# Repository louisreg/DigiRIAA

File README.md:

# DigiRIAA
A small and compact RIAA preamp with digital outputs
blablabla

## Description
schematic etc

## PCB

## Measures

## TODO
  - Get rid of STM32 HAL lib, add CMAKE, clean etc. 
  - Remove TL072 buffer from PCB
  - Remove USB-C connector

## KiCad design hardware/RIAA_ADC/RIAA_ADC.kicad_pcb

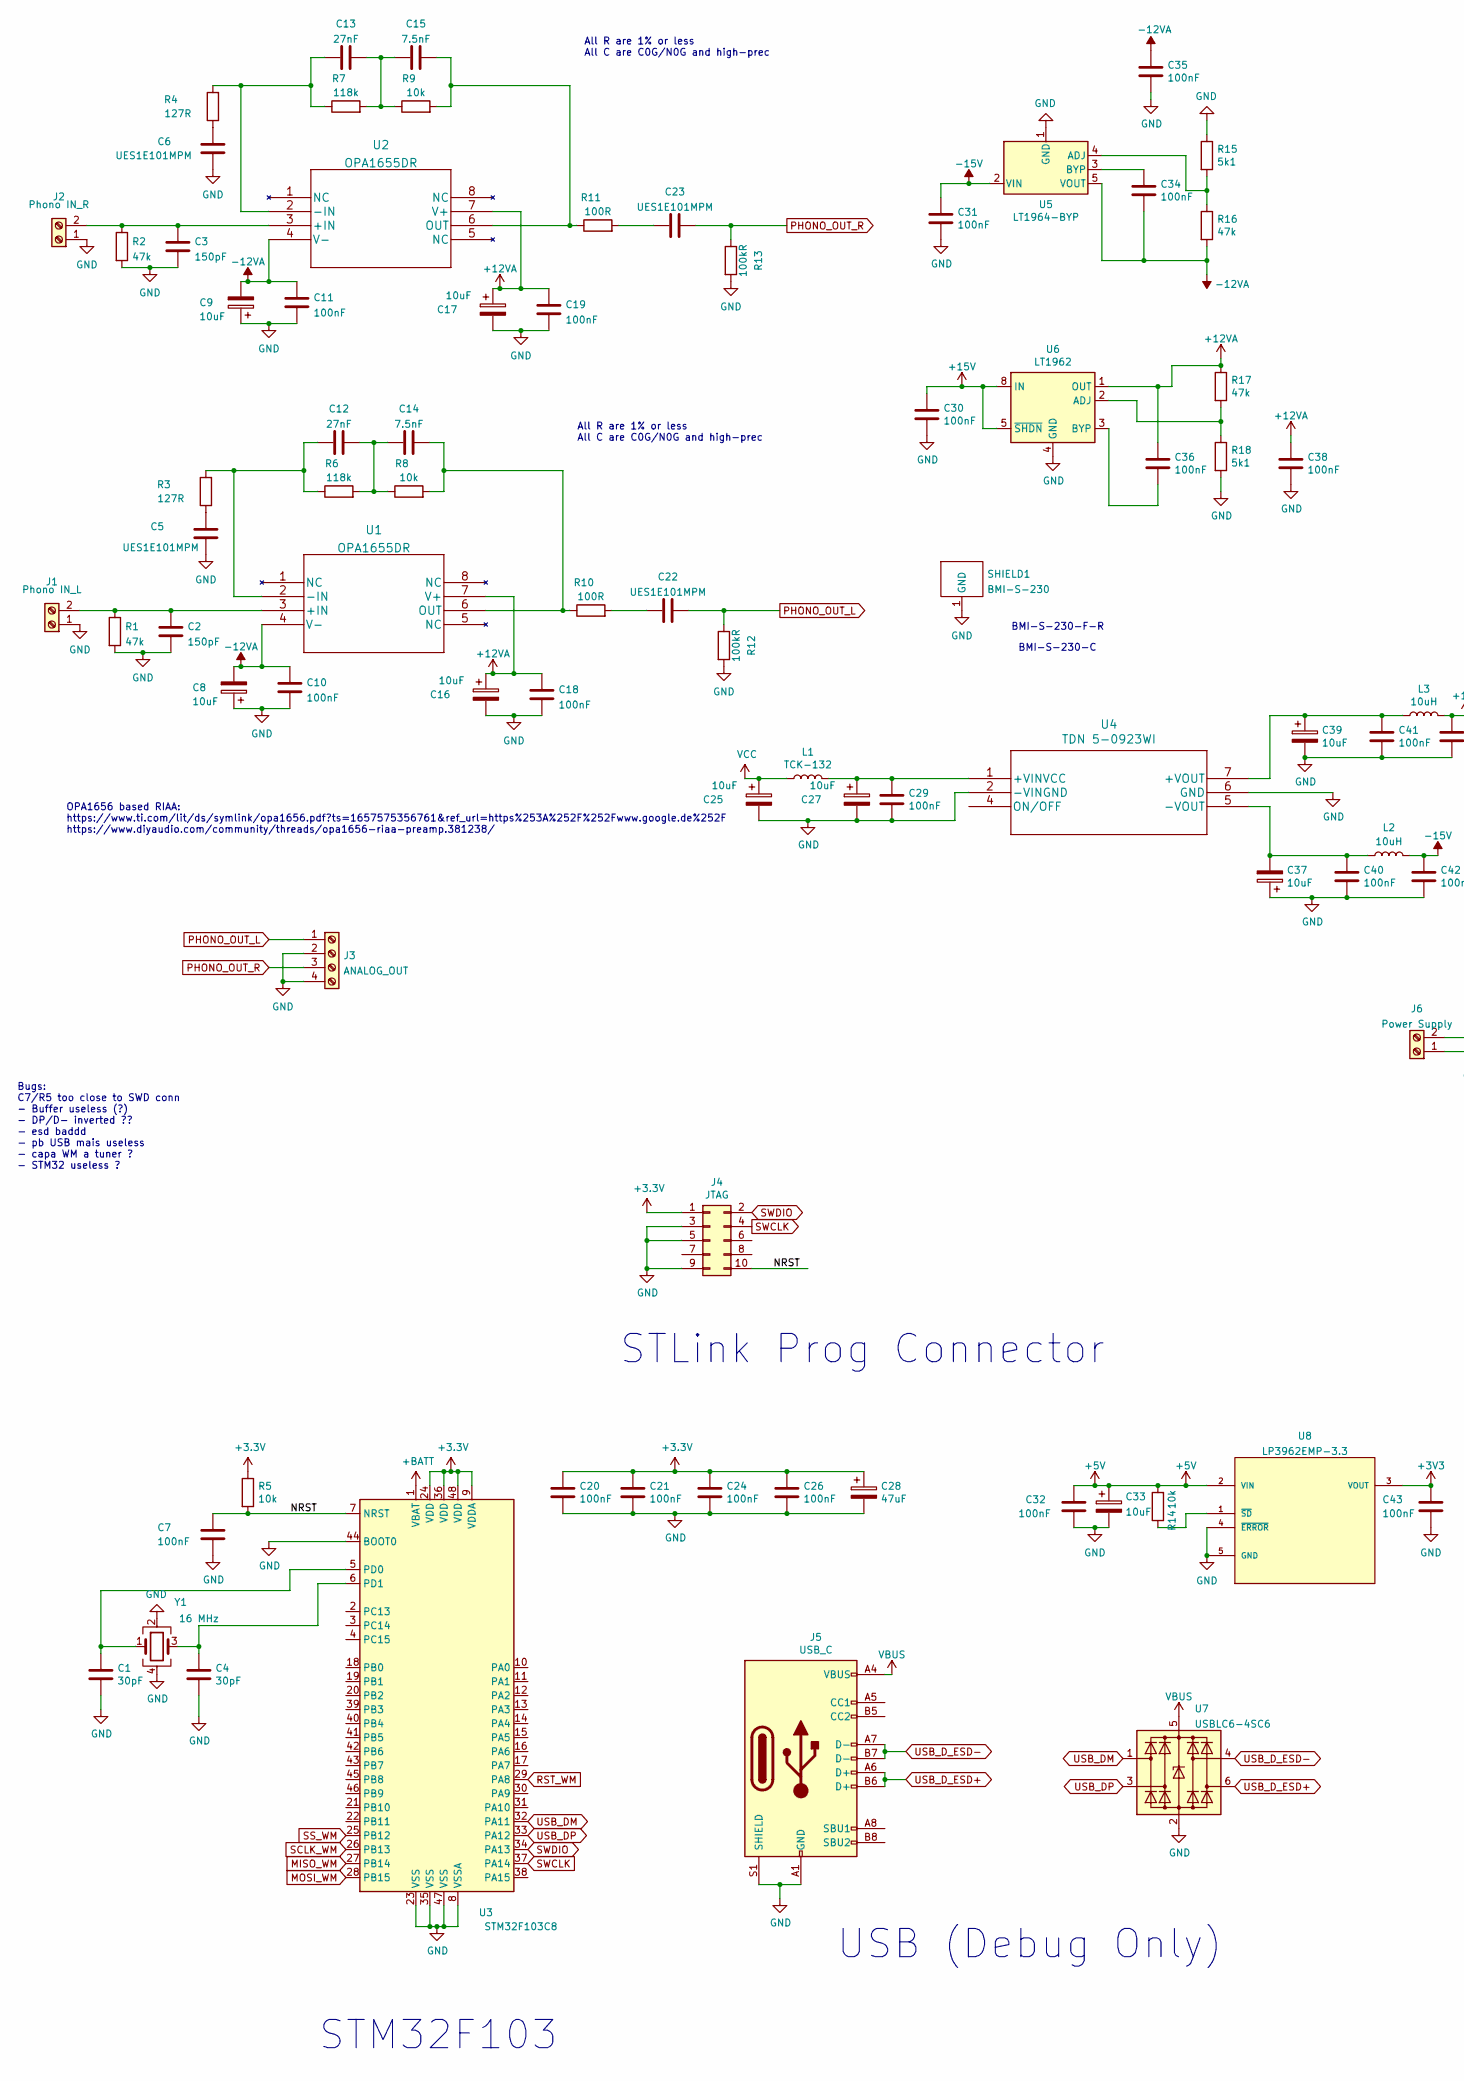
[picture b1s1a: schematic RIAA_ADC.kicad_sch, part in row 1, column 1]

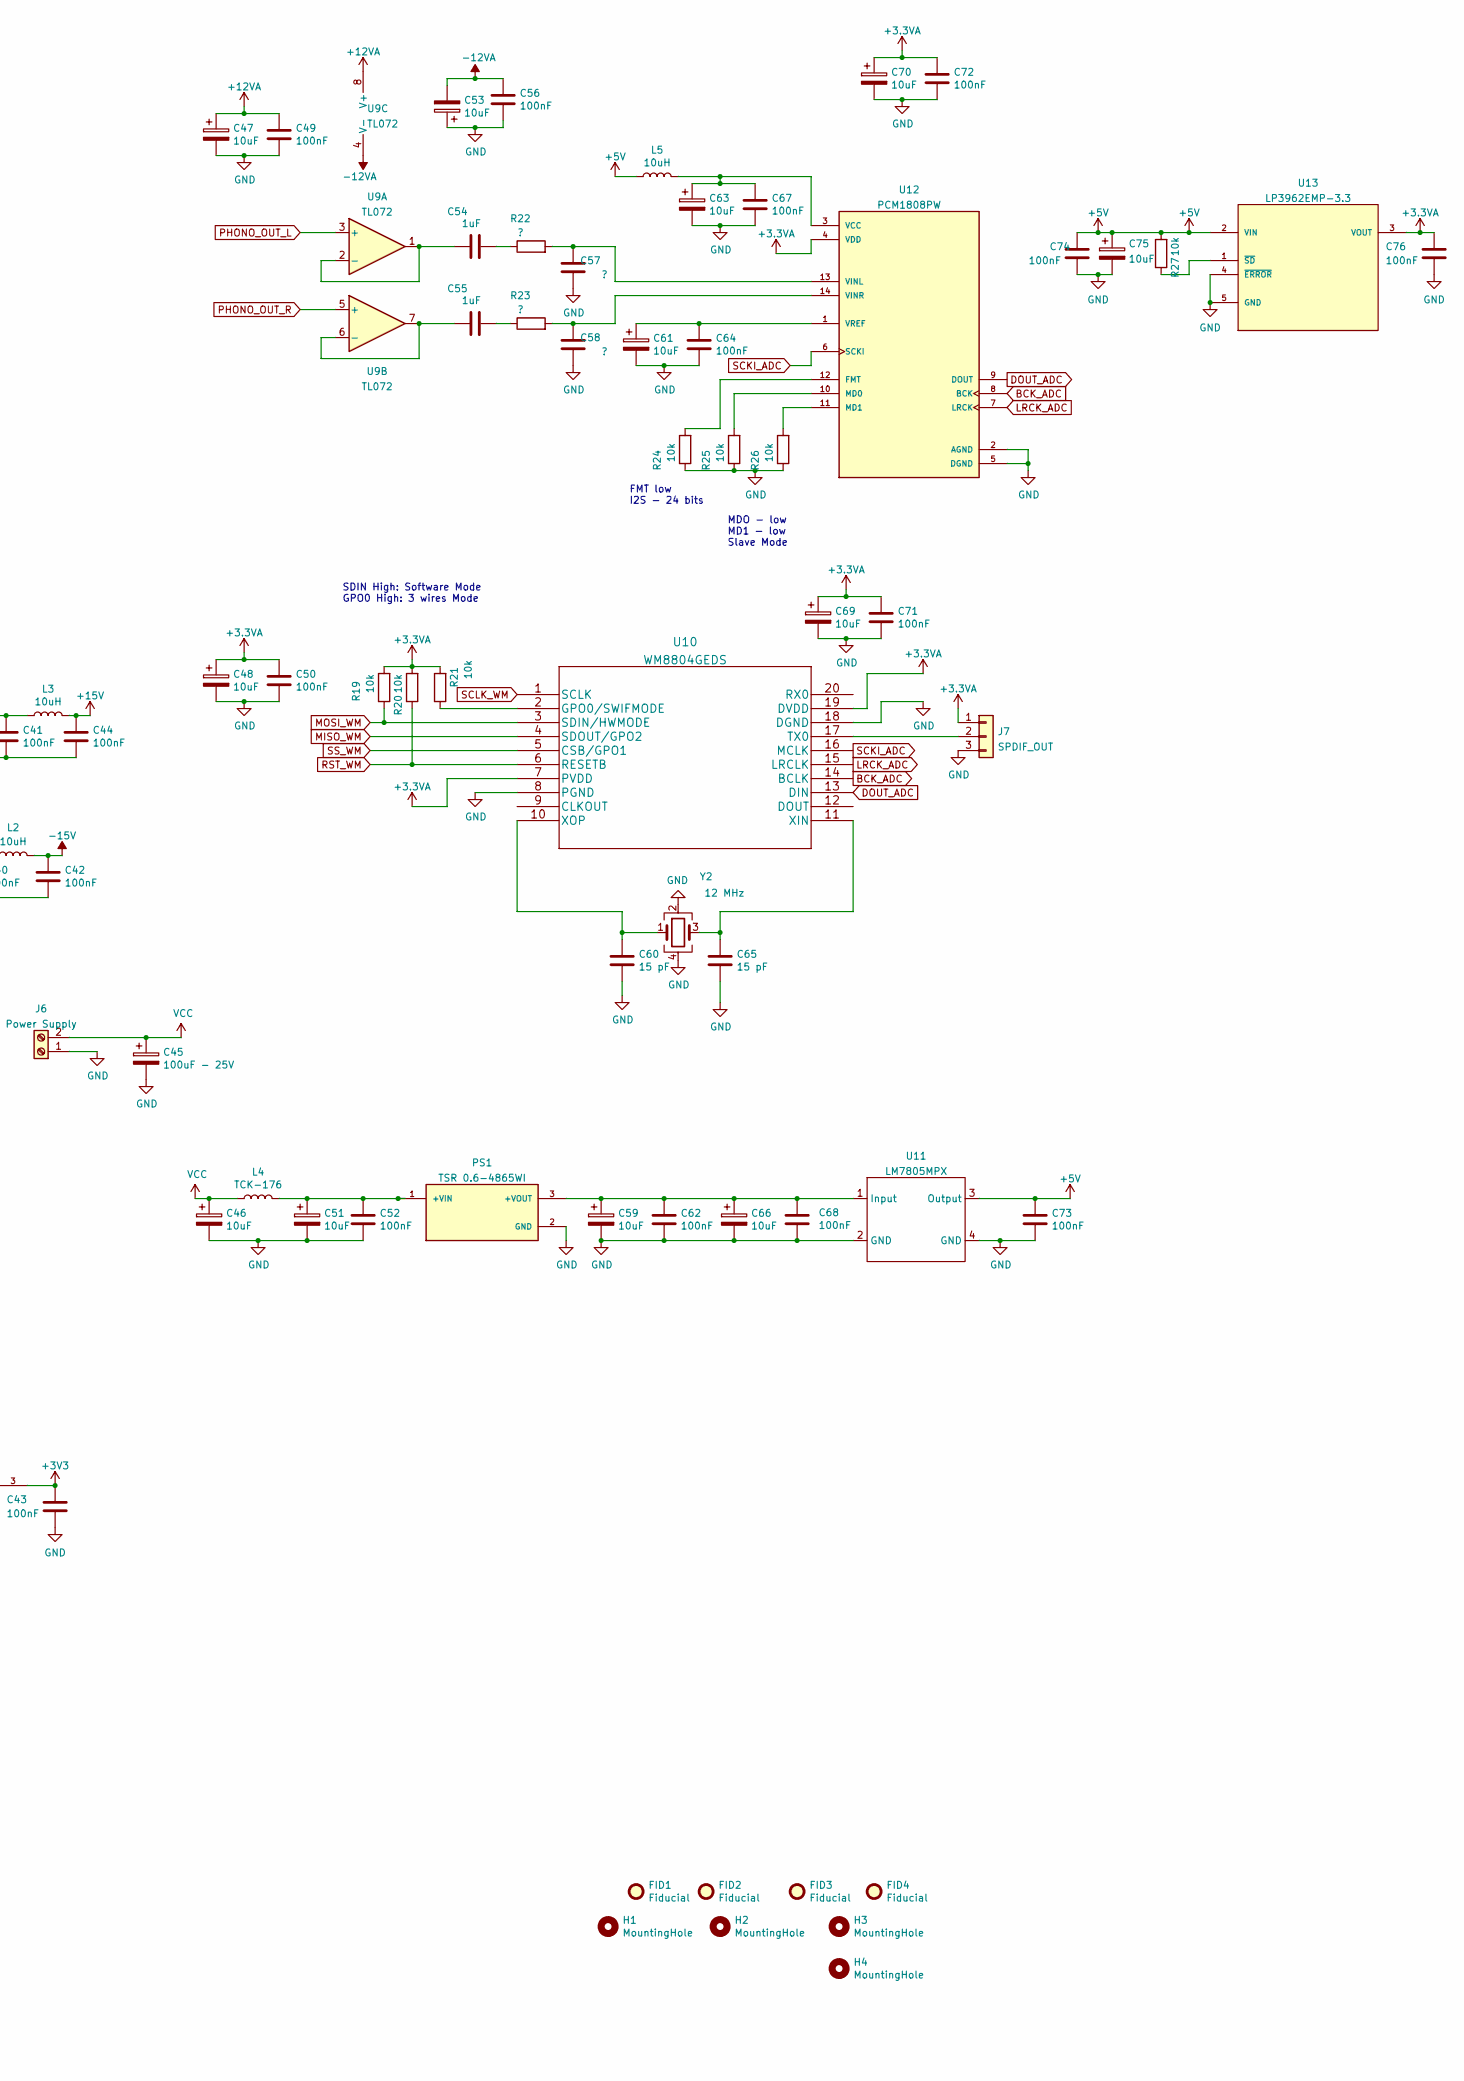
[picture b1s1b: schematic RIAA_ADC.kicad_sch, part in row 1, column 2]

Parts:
C1, C4: 30pF; C_0603_1608Metric
C2, C3: 150pF; C_0603_1608Metric
C5, C6, C22, C23: UES1E101MPM; CP_Radial_D8.0mm_P5.00mm
C7, C10, C11, C18, C19, C20, C21, C24, C26, C29, C30, C31, C32, C34, C35, C36, C38, C40, C41, C42, C43, C44, C49, C50, C52, C56, C62, C64, C67, C68, C71, C72, C73, C74, C76: 100nF; C_0603_1608Metric
C8, C9, C16, C17, C25, C27, C33, C37, C39, C46, C47, C48, C51, C53, C59, C61, C63, C66, C69, C70, C75: 10uF; CP_EIA-3528-21_Kemet-B
C12, C13: 27nF; C_1210_3225Metric_Pad1.33x2.70mm_HandSolder
C14, C15: 7.5nF; C_1210_3225Metric_Pad1.33x2.70mm_HandSolder
C28: 47uF; CP_EIA-3528-21_Kemet-B
C45: 100uF - 25V; CP_Radial_D8.0mm_P5.00mm
C54, C55: 1uF; C_1210_3225Metric_Pad1.33x2.70mm_HandSolder
C57, C58: ?; C_0603_1608Metric
C60, C65: 15 pF; C_0603_1608Metric
FID1, FID2, FID3, FID4: Fiducial; Fiducial_0.5mm_Mask1mm
H1, H2, H3, H4: MountingHole; MountingHole_3mm
J1: Phono IN_L; TerminalBlock_TE_282834-2_1x02_P2.54mm_Horizontal
J2: Phono IN_R; TerminalBlock_TE_282834-2_1x02_P2.54mm_Horizontal
J3: ANALOG_OUT; TerminalBlock_TE_282834-4_1x04_P2.54mm_Horizontal
J4: JTAG; PinHeader_2x05_P1.27mm_Vertical_SMD
J5: USB_C; USB_C_Receptacle_XKB_U262-16XN-4BVC11
J6: Power Supply; TerminalBlock_bornier-2_P5.08mm
J7: SPDIF_OUT; TerminalBlock_TE_282834-3_1x03_P2.54mm_Horizontal
L1: TCK-132
L2, L3, L5: 10uH; L_1210_3225Metric
L4: TCK-176
PS1: TSR 0.6-4865WI; CONV_TSR_0.6-4833WI; PARTREV Apr 27, 2020
R1, R2, R16, R17: 47k; R_0603_1608Metric
R3, R4: 127R; R_0603_1608Metric
R5, R8, R9, R14, R19, R20, R21, R24, R25, R26, R27: 10k; R_0603_1608Metric
R6, R7: 118k; R_0603_1608Metric
R10, R11: 100R; R_0603_1608Metric
R12, R13: 100kR; R_0603_1608Metric
R15, R18: 5k1; R_0603_1608Metric
R22, R23: ?; R_0603_1608Metric
SHIELD1: BMI-S-230; Laird_Technologies_BMI-S-230-F_50.8x38.1mm
U1, U2: OPA1655DR
U3: STM32F103C8; LQFP-48_7x7mm_P0.5mm
U4: TDN 5-0923WI; Converter_DCDC_TRACO_TDN_5-xxxxWI_THT
U5: LT1964-BYP; TSOT-23-5
U6: LT1962; MSOP-8_3x3mm_P0.65mm
U7: USBLC6-4SC6; SOT-23-6
U8, U13: LP3962EMP-3.3; SOT150P696X180-5N; MPN LP3962EMP-3.3
U9: TL072; TSSOP-8_4.4x3mm_P0.65mm
U10: WM8804GEDS
U11: LM7805MPX; SOT-223
U12: PCM1808PW; SOP65P640X120-14N; PARTREV B
Y1: 16 MHz; Crystal_SMD_3225-4Pin_3.2x2.5mm_HandSoldering
Y2: 12 MHz; Crystal_SMD_3225-4Pin_3.2x2.5mm_HandSoldering

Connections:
+3.3VA: C48.1, C50.1, C69.1, C70.1, C71.1, C72.1, C76.1, J7.1, R19.2, R20.2, R21.2, U10.7 (PVDD), U10.19 (DVDD), U12.4 (VDD), U13.3 (VOUT)
+5V: C32.1, C33.1, C73.1, C74.1, C75.1, L5.1, R14.2, R27.2, U8.2 (VIN), U11.3 (Output), U13.2 (VIN)
+12VA: C16.1, C17.1, C18.1, C19.1, C36.1, C38.1, C47.1, C49.1, R17.1, U1.7 (V+), U2.7 (V+), U6.1 (OUT), U9.8 (V+)
+15V: C30.1, C44.1, L3.2, U6.5 (~SHDN), U6.8 (IN)
+BATT: U3.1 (VBAT)
-12VA: C8.2, C9.2, C10.1, C11.1, C34.2, C35.1, C53.2, C56.1, R16.2, U1.4 (V-), U2.4 (V-), U5.5 (VOUT), U9.4 (V-)
-15V: C31.1, C42.1, L2.2, U5.2 (VIN)
/NRST: C7.2, J4.10, R5.2, U3.7 (NRST)
BCK_ADC: U10.14 (BCLK), U12.8 (BCK)
DOUT_ADC: U10.13 (DIN), U12.9 (DOUT)
GND: C1.1, C2.2, C3.2, C4.1, C5.2, C6.2, C7.1, C8.1, C9.1, C10.2, C11.2, C16.2, C17.2, C18.2, C19.2, C20.1, C21.1, C24.1, C25.2, C26.1, C27.2, C28.2, C29.2, C30.2, C31.2, C32.2, C33.2, C35.2, C37.1, C38.2, C39.2, C40.2, C41.2, C42.2, C43.2, C44.2, C45.2, C46.2, C47.2, C48.2, C49.2, C50.2, C51.2, C52.2, C53.1, C56.2, C57.1, C58.1, C59.2, C60.1, C61.2, C62.2, C63.2, C64.2, C65.1, C66.2, C67.2, C68.2, C69.2, C70.2, C71.2, C72.2, C73.2, C74.2, C75.2, C76.2, J1.1, J2.1, J3.2, J3.4, J4.3, J4.5, J4.9, J5.A1 (GND), J5.A12 (GND), J5.B1 (GND), J5.B12 (GND), J5.S1 (SHIELD), J6.1, J7.3, PS1.2 (GND), R1.2, R2.2, R12.2, R13.2, R15.1, R18.2, R24.1, R25.1, R26.1, SHIELD1.1 (GND), U3.8 (VSSA), U3.23 (VSS), U3.35 (VSS), U3.44 (BOOT0), U3.47 (VSS), U4.2 (-VINGND), U4.6 (GND), U5.1 (GND), U6.4 (GND), U7.2 (GND), U8.4 (~ERROR), U8.5 (GND), U10.8 (PGND), U10.18 (DGND), U11.2 (GND), U11.4 (GND), U12.2 (AGND), U12.5 (DGND), U13.4 (~ERROR), U13.5 (GND), Y1.2, Y1.4, Y2.2, Y2.4
LRCK_ADC: U10.15 (LRCLK), U12.7 (LRCK)
MISO_WM: U3.27 (PB14), U10.4 (SDOUT/GPO2)
MOSI_WM: R19.1, U3.28 (PB15), U10.3 (SDIN/HWMODE)
unnamed: C1.2, U3.5 (PD0), Y1.1
unnamed: C2.1, J1.2, R1.1, U1.3 (+IN)
unnamed: C3.1, J2.2, R2.1, U2.3 (+IN)
unnamed: C4.2, U3.6 (PD1), Y1.3
unnamed: C5.1, R3.1
unnamed: C6.1, R4.1
unnamed: C12.1, R3.2, R6.1, U1.2 (-IN)
unnamed: C12.2, C14.1, R6.2, R8.1
unnamed: C13.1, R4.2, R7.1, U2.2 (-IN)
unnamed: C13.2, C15.1, R7.2, R9.1
unnamed: C14.2, R8.2, R10.1, U1.6 (OUT)
unnamed: C15.2, R9.2, R11.1, U2.6 (OUT)
unnamed: C22.1, R10.2
unnamed: C23.1, R11.2
unnamed: C27.1, C29.1, L1.2, U4.1 (+VINVCC)
unnamed: C34.1, U5.3 (BYP)
unnamed: C36.2, U6.3 (BYP)
unnamed: C37.2, C40.1, L2.1, U4.5 (-VOUT)
unnamed: C39.1, C41.1, L3.1, U4.7 (+VOUT)
unnamed: C51.1, C52.1, L4.2, PS1.1 (+VIN)
unnamed: C54.1, U9.1, U9.2 (-)
unnamed: C54.2, R22.1
unnamed: C55.1, U9.6 (-), U9.7
unnamed: C55.2, R23.1
unnamed: C57.2, R22.2, U12.13 (VINL)
unnamed: C58.2, R23.2, U12.14 (VINR)
unnamed: C59.1, C62.1, C66.1, C68.1, PS1.3 (+VOUT), U11.1 (Input)
unnamed: C60.2, U10.10 (XOP), Y2.1
unnamed: C61.1, C64.1, U12.1 (VREF)
unnamed: C63.1, C67.1, L5.2, U12.3 (VCC)
unnamed: C65.2, U10.11 (XIN), Y2.3
unnamed: J7.2, U10.17 (TX0)
unnamed: R14.1, U8.1 (~SD)
unnamed: R15.2, R16.1, U5.4 (ADJ)
unnamed: R17.2, R18.1, U6.2 (ADJ)
unnamed: R21.1, U10.2 (GPO0/SWIFMODE)
unnamed: R24.2, U12.12 (FMT)
unnamed: R25.2, U12.10 (MD0)
unnamed: R26.2, U12.11 (MD1)
unnamed: R27.1, U13.1 (~SD)
PHONO_OUT_L: C22.2, J3.1, R12.1, U9.3 (+)
PHONO_OUT_R: C23.2, J3.3, R13.1, U9.5 (+)
RST_WM: R20.1, U3.29 (PA8), U10.6 (RESETB)
SCKI_ADC: U10.16 (MCLK), U12.6 (SCKI)
SCLK_WM: U3.26 (PB13), U10.1 (SCLK)
SS_WM: U3.25 (PB12), U10.5 (CSB/GPO1)
SWCLK: J4.4, U3.37 (PA14)
SWDIO: J4.2, U3.34 (PA13)
USB_DM: U3.32 (PA11), U7.1 (I/O1)
USB_DP: U3.33 (PA12), U7.3 (I/O2)
USB_D_ESD+: J5.A6 (D+), J5.B6 (D+), U7.6 (I/O4)
USB_D_ESD-: J5.A7 (D-), J5.B7 (D-), U7.4 (I/O3)
VBUS: J5.A4 (VBUS), J5.A9 (VBUS), J5.B4 (VBUS), J5.B9 (VBUS), U7.5 (VBUS)
VCC: C25.1, C45.1, C46.1, J6.2, L1.1, L4.1

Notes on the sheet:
SDIN High: Software Mode GPO0 High: 3 wires Mode
OPA1656 based RIAA: https://www.ti.com/lit/ds/symlink/opa1656.pdf?ts=1657575356761&ref_url=https%253A%252F%252Fwww.google.de%252F https://www.diyaudio.com/community/threads/opa1656-riaa-preamp.381238/
BMI-S-230-C
STM32F103
All R are 1% or less All C are C0G/N0G and high-prec
Bugs: C7/R5 too close to SWD conn - Buffer useless (?) - DP/D- inverted ?? - esd baddd - pb USB mais useless - capa WM a tuner ? - STM32 useless ?
FMT low I2S - 24 bits
USB (Debug Only)
MDO - low MD1 - low Slave Mode
BMI-S-230-F-R
STLink Prog Connector

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
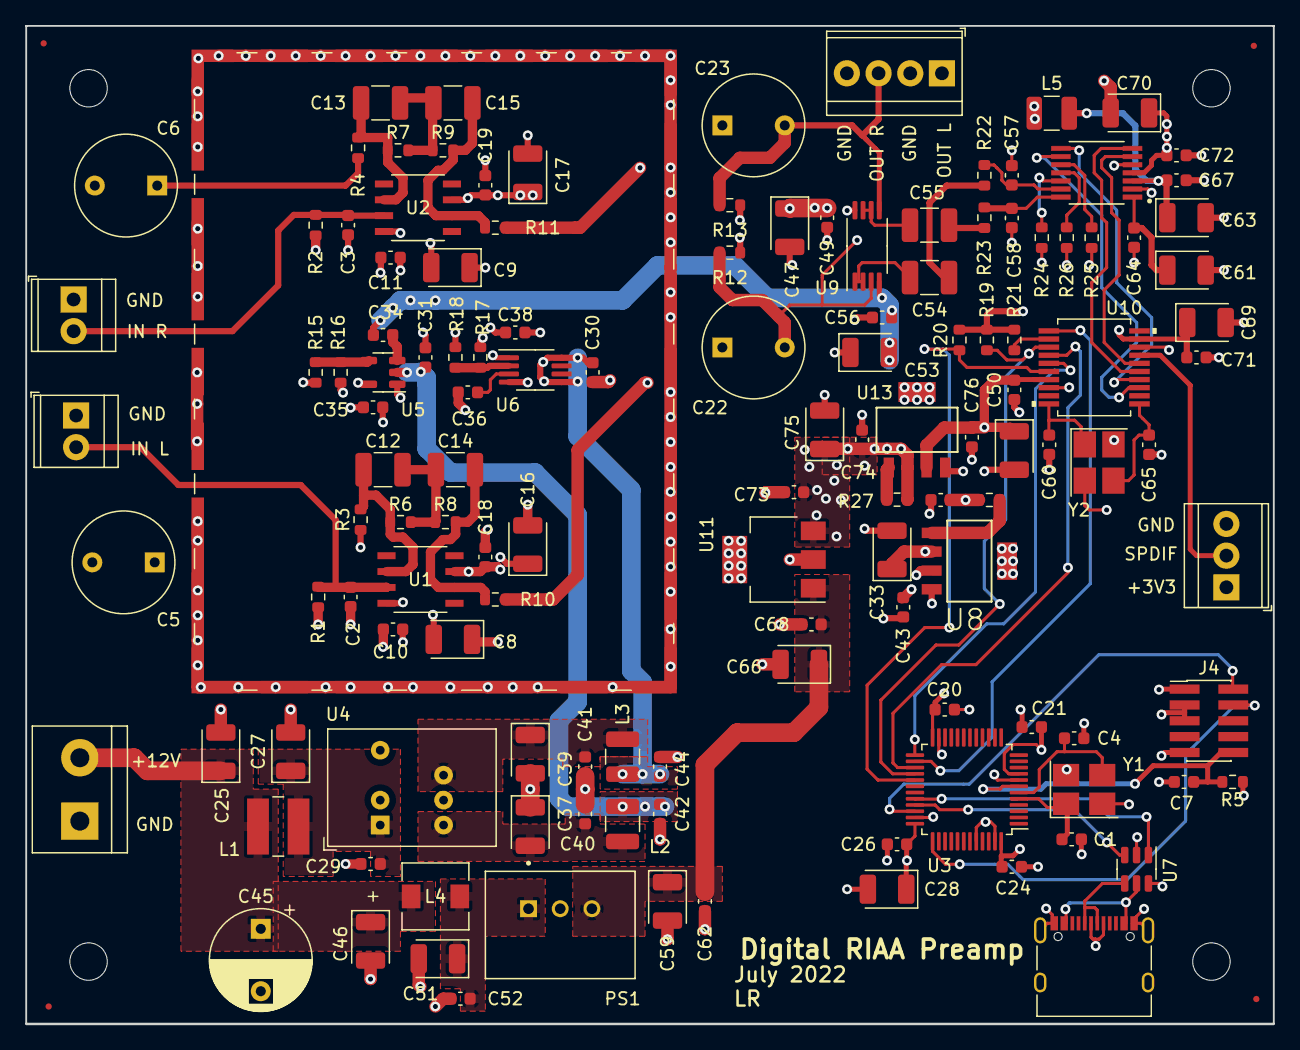
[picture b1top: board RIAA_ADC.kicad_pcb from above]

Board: 4 copper layers, 100.0 x 80.0 mm, 140 parts (0 on the bottom side), 68 nets.

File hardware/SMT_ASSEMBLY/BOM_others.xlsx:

Comment | Designator | Footprint
UES1E101MPM | C22,C23,C5,C6 | CP_Radial_D8.0mm_P5.00mm | x
7.5nF | C15,C14 | C_1210_3225Metric_Pad1.33x2.70mm_HandSolder | OK
TDN 5-0923WI | U4 | Converter_DCDC_TRACO_TDN_5-xxxxWI_THT | OK
? | R17,R18,R16,R22,R15,R23 | R_0603_1608Metric | OK
LM7805MPX | U11 | SOT-223 | in stock?
? | C57,C58 | C_0603_1608Metric | OK
10uH | L5,L2,L3 | L_1210_3225Metric | OK
OPA1655DR | U1,U2 | OPA1655DR | TI
27nF | C13,C12 | C_1210_3225Metric_Pad1.33x2.70mm_HandSolder | OK
150pF | C3,C2 | C_0603_1608Metric | OK
12 MHz | Y2 | Crystal_SMD_3225-4Pin_3.2x2.5mm_HandSoldering | OK
1uF | C54,C55 | C_1210_3225Metric_Pad1.33x2.70mm_HandSolder | OK
TCK-176 | L4 | TCK-176 | x
LP3962EMP-3.3 | U8,U13 | SOT150P696X180-5N | x
47k | R1,R2 | R_0603_1608Metric | OK
Phono IN_L | J1 | TerminalBlock_TE_282834-2_1x02_P2.54mm_Horizontal | OK
LT1964-BYP | U5 | TSOT-23-5 | OK
ANALOG_OUT | J3 | TerminalBlock_TE_282834-4_1x04_P2.54mm_Horizontal | OK
USBLC6-4SC6 | U7 | SOT-23-6 | OK
47uF | C28 | CP_EIA-3528-21_Kemet-B | OK
100R | R11,R10 | R_0603_1608Metric | OK
16 MHz | Y1 | Crystal_SMD_3225-4Pin_3.2x2.5mm_HandSoldering | OK
Phono IN_R | J2 | TerminalBlock_TE_282834-2_1x02_P2.54mm_Horizontal | OK
100kR | R13,R12 | R_0603_1608Metric | OK
WM8804GEDS | U10 | WM8804GEDS | OK
TSR 0.6-4865WI | PS1 | CONV_TSR_0.6-4833WI | OK
USB_C | J5 | USB_C_Receptacle_XKB_U262-16XN-4BVC11 | OK
JTAG | J4 | PinHeader_2x05_P1.27mm_Vertical_SMD | OK
30pF | C4,C1 | C_0603_1608Metric | OK
SPDIF_OUT | J7 | TerminalBlock_TE_282834-3_1x03_P2.54mm_Horizontal | x
100uF - 25V | C45 | CP_Radial_D8.0mm_P5.00mm | x
BMI-S-230 | SHIELD1 | Laird_Technologies_BMI-S-230-F_50.8x38.1mm | OK
118k | R6,R7 | R_0603_1608Metric | OK
TCK-132 | L1 | TCK-132 | OK
15 pF | C60,C65 | C_0603_1608Metric | OK
Power Supply | J6 | TerminalBlock_bornier-2_P5.08mm | x
TL072 | U9 | TSSOP-8_4.4x3mm_P0.65mm | x
LT1962 | U6 | MSOP-8_3x3mm_P0.65mm | x

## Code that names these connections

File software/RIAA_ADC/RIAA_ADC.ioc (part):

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Mcu.Name=STM32F103C(8-B)Tx
Mcu.Package=LQFP48
Mcu.UserName=STM32F103C8Tx
PA13.Mode=Trace_Asynchronous_SW
PA13.Signal=SYS_JTMS-SWDIO
PA14.Mode=Trace_Asynchronous_SW
PA14.Signal=SYS_JTCK-SWCLK
PA8.GPIOParameters=GPIO_Label
PA8.GPIO_Label=RST_WM
PA8.Signal=GPIO_Output
PB12.GPIOParameters=GPIO_Label
PB12.GPIO_Label=SS_WM
PB12.Signal=GPIO_Output
PB13.GPIOParameters=GPIO_Label
PB13.GPIO_Label=SCLK_WM
PB13.Mode=Full_Duplex_Master
PB13.Signal=SPI2_SCK
PB14.GPIOParameters=GPIO_Label
PB14.GPIO_Label=MISO_WM
PB14.Mode=Full_Duplex_Master
PB14.Signal=SPI2_MISO
PB15.GPIOParameters=GPIO_Label
PB15.GPIO_Label=MOSI_WM
PB15.Mode=Full_Duplex_Master
PB15.Signal=SPI2_MOSI
PB3.Mode=Trace_Asynchronous_SW
PB3.Signal=SYS_JTDO-TRACESWO
PD0-OSC_IN.Mode=HSE-External-Oscillator
PD0-OSC_IN.Signal=RCC_OSC_IN
PD1-OSC_OUT.Mode=HSE-External-Oscillator
PD1-OSC_OUT.Signal=RCC_OSC_OUT
RCC.HSEDivPLL=RCC_HSE_PREDIV_DIV2
RCC.HSE_VALUE=16000000
RCC.SYSCLKFreq_VALUE=64000000
RCC.SYSCLKSource=RCC_SYSCLKSOURCE_PLLCLK
board=custom

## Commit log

2023-10-18 add software files

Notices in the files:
parts and their libraries:
Copyright 2021 Accelerated Designs. All rights reserved.
